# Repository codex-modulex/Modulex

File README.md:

# Modulex

All modulex listed on our webshop

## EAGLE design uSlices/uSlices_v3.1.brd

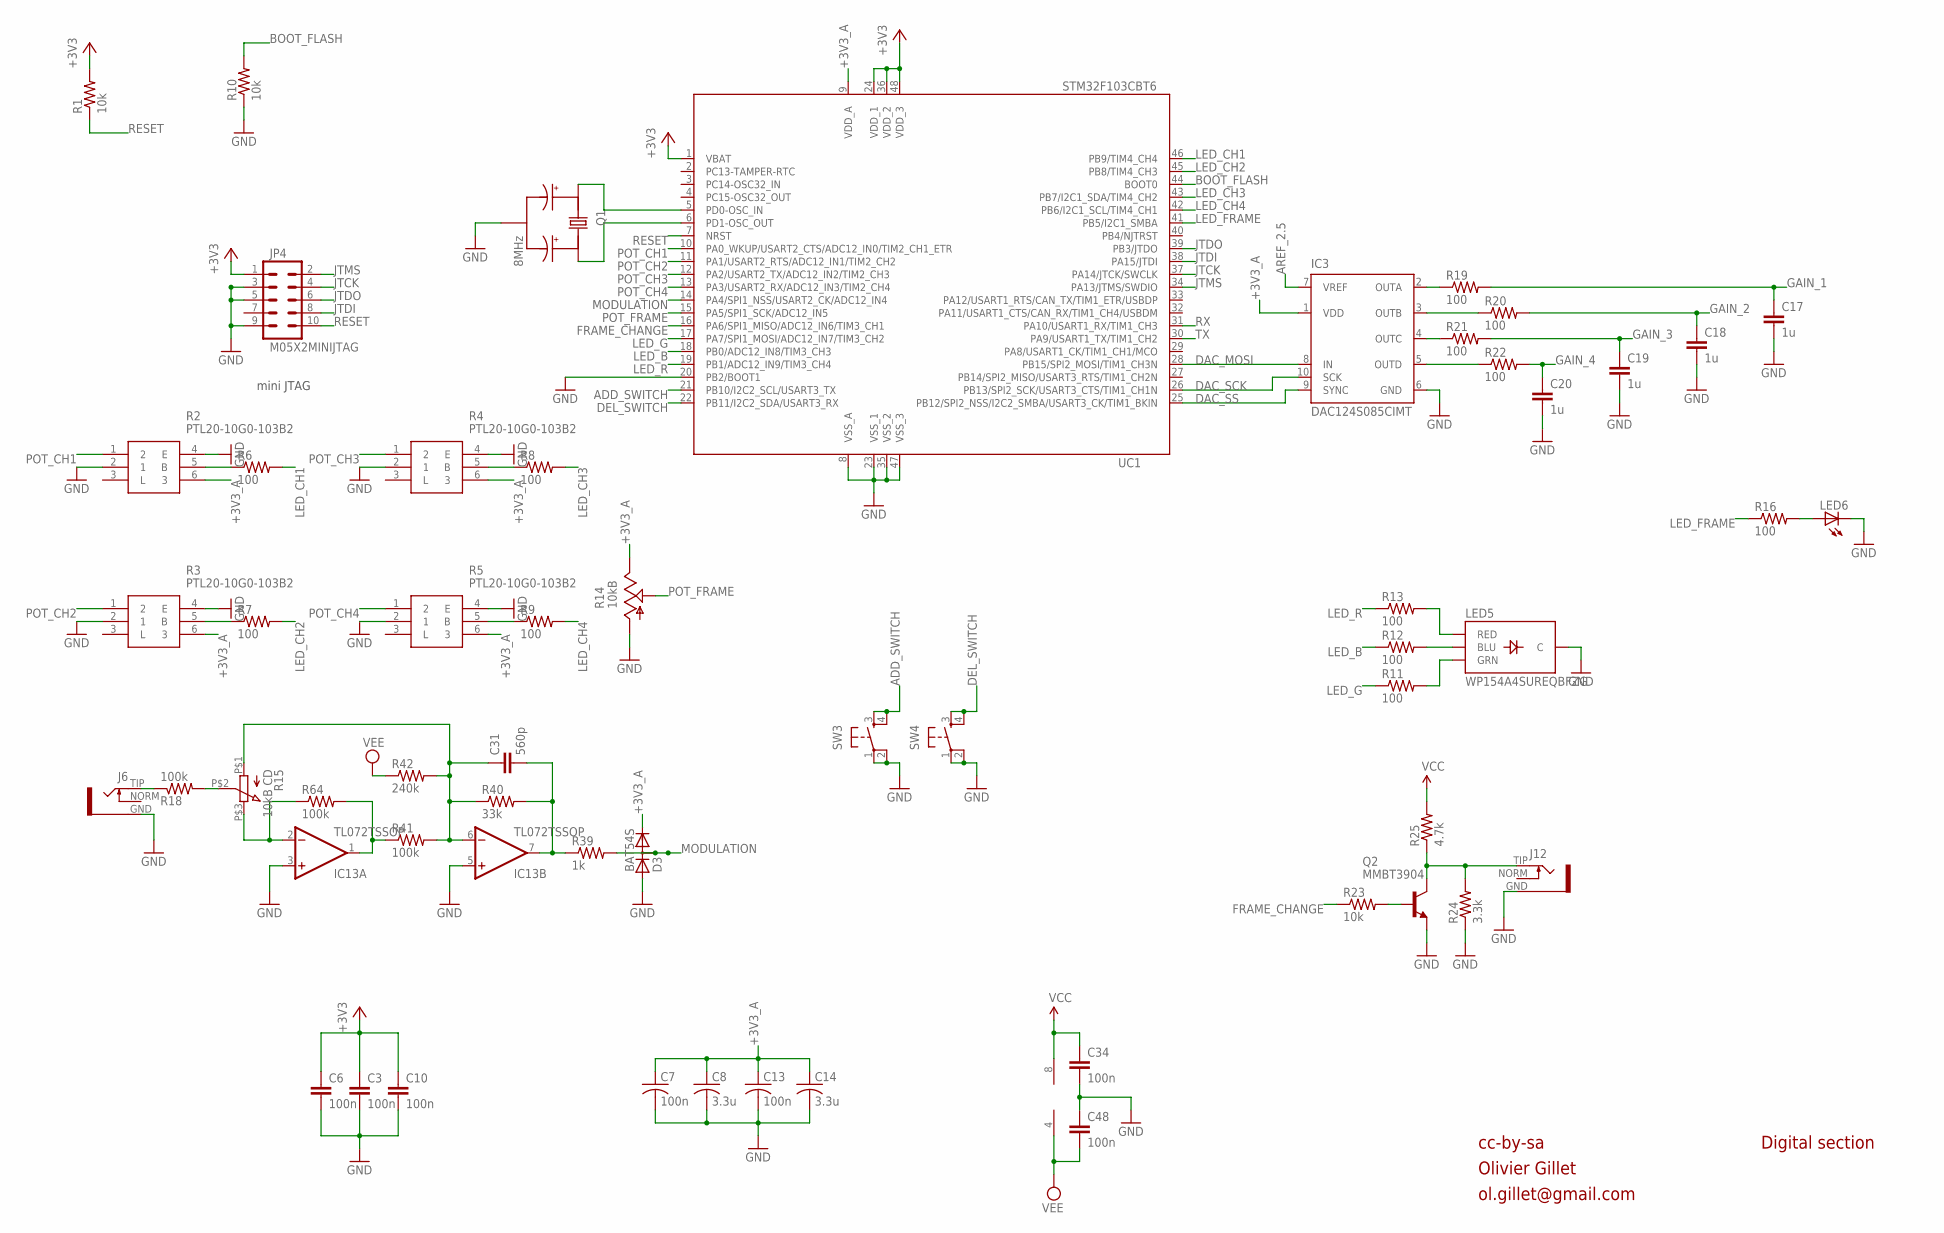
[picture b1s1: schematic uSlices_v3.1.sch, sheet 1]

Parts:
C3, C6, C10, C34, C48: 100n; PARTS_AMAN_RESISTOR_0603
C7, C13: 100n; C0603
C8, C14: 3.3u; C0603
C17, C18, C19, C20: 1u; PARTS_AMAN_RESISTOR_0603
C31: 560p; PARTS_AMAN_RESISTOR_0603
D3: BAT54S; SOT23
IC3: DAC124S085CIMT; MSOP10
IC13: TL072TSSOP; TSSOP-8
J6, J12: INSTRUO_S_JACK_S2_INV
JP4: M05X2MINIJTAG; 2X5-1.27
LED5: WP154A4SUREQBFZG; LED-TRICOLOR-THROUGHHOLE
LED6: LED3MM
Q1: 8MHz; INSTRUO_CRYSTAL_SMALLER
Q2: MMBT3904; SOT23-BEC
R1, R10, R23: 10k; PARTS_AMAN_RESISTOR_0603
R2, R3, R4, R5: PTL20-10G0-103B2; PTL2010G0103B2
R6, R7, R8, R9, R11, R12, R13, R16, R19, R20, R21, R22: 100; PARTS_AMAN_RESISTOR_0603
R14: 10kB; ALPS_POT_VERTICAL_PS
R15: 10kB CD; INSTRUO_Q-POT2
R18: 100k; R0603
R24: 3.3k; PARTS_AMAN_RESISTOR_0603
R25: 4.7k; PARTS_AMAN_RESISTOR_0603
R39: 1k; PARTS_AMAN_RESISTOR_0603
R40: 33k; PARTS_AMAN_RESISTOR_0603
R41, R64: 100k; PARTS_AMAN_RESISTOR_0603
R42: 240k; PARTS_AMAN_RESISTOR_0603
SW3, SW4: SPARKFUN_TAC_SWITCHPTH; SPARKFUN_TACTILE-PTH
UC1: STM32F103CBT6; LQFP48

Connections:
+3V3: C3.1, C6.1, C10.1, JP4.1, R1.2, UC1.1 (VBAT), UC1.24 (VDD_1), UC1.36 (VDD_2), UC1.48 (VDD_3); also elsewhere on the board
+3V3_A: C7.1, C8.1, C13.1, C14.1, D3.2 (C), IC3.1 (VDD), R2.6 (3), R3.6 (3), R4.6 (3), R5.6 (3), R14.P$1 (E), UC1.9 (VDD_A); also elsewhere on the board
ADD_SWITCH: SW3.3, SW3.4, UC1.21 (PB10/I2C2_SCL/USART3_TX)
AREF_2.5: IC3.7 (VREF); also elsewhere on the board
BOOT_FLASH: R10.2, UC1.44 (BOOT0)
DAC_MOSI: IC3.8 (IN), UC1.28 (PB15/SPI2_MOSI/TIM1_CH3N)
DAC_SCK: IC3.10 (SCK), UC1.26 (PB13/SPI2_SCK/USART3_CTS/TIM1_CH1N)
DAC_SS: IC3.9 (SYNC), UC1.25 (PB12/SPI2_NSS/I2C2_SMBA/USART3_CK/TIM1_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)
DEL_SWITCH: SW4.3, SW4.4, UC1.22 (PB11/I2C2_SDA/USART3_RX)
FRAME_CHANGE: R23.1, UC1.16 (PA6/SPI1_MISO/ADC12_IN6/TIM3_CH1)
GAIN_1: C17.1, R19.2; also elsewhere on the board
GAIN_2: C18.1, R20.2; also elsewhere on the board
GAIN_3: C19.1, R21.2; also elsewhere on the board
GAIN_4: C20.1, R22.2; also elsewhere on the board
GND: C3.2, C6.2, C7.2, C8.2, C10.2, C13.2, C14.2, C17.2, C18.2, C19.2, C20.2, C34.2, C48.1, D3.1 (A), IC3.6 (GND), IC13.3 (+IN), IC13.5 (+IN), J6.GND, J12.GND, JP4.3, JP4.5, JP4.9, LED5.GND (C), LED6.K (C), Q1.GND, Q2.E, R2.2 (1), R2.4 (E), R3.2 (1), R3.4 (E), R4.2 (1), R4.4 (E), R5.2 (1), R5.4 (E), R10.1, R14.P$3 (A), R24.1, SW3.1, SW3.2, SW4.1, SW4.2, UC1.8 (VSS_A), UC1.20 (PB2/BOOT1), UC1.23 (VSS_1), UC1.35 (VSS_2), UC1.47 (VSS_3); also elsewhere on the board
JTCK: JP4.4, UC1.37 (PA14/JTCK/SWCLK)
JTDI: JP4.8, UC1.38 (PA15/JTDI)
JTDO: JP4.6, UC1.39 (PB3/JTDO)
JTMS: JP4.2, UC1.34 (PA13/JTMS/SWDIO)
LED_B: R12.1, UC1.18 (PB0/ADC12_IN8/TIM3_CH3)
LED_CH1: R6.2, UC1.46 (PB9/TIM4_CH4)
LED_CH2: R7.2, UC1.45 (PB8/TIM4_CH3)
LED_CH3: R8.2, UC1.43 (PB7/I2C1_SDA/TIM4_CH2)
LED_CH4: R9.2, UC1.42 (PB6/I2C1_SCL/TIM4_CH1)
LED_FRAME: R16.1, UC1.41 (PB5/I2C1_SMBA)
LED_G: R11.1, UC1.17 (PA7/SPI1_MOSI/ADC12_IN7/TIM3_CH2)
LED_R: R13.1, UC1.19 (PB1/ADC12_IN9/TIM3_CH4)
MODULATION: D3.3 (AC), R39.2, UC1.14 (PA4/SPI1_NSS/USART2_CK/ADC12_IN4)
unnamed: IC13.2 (-IN), R15.P$3 (3), R64.1
unnamed: R15.P$2 (2), R18.2
unnamed: R2.5 (B), R6.1
unnamed: Q1.X1, UC1.5 (PD0-OSC_IN)
unnamed: Q1.X2, UC1.6 (PD1-OSC_OUT)
unnamed: IC13.1 (OUT), R41.1, R64.2
unnamed: J6.TIP, R18.1
unnamed: C31.2, IC13.7 (OUT), R39.1, R40.2
unnamed: C31.1, IC13.6 (-IN), R15.P$1 (1), R40.1, R41.2, R42.2
unnamed: LED6.A, R16.2
unnamed: LED5.RED, R13.2
unnamed: LED5.BLU, R12.2
unnamed: LED5.GRN, R11.2
unnamed: R3.5 (B), R7.1
unnamed: IC3.2 (OUTA), R19.1
unnamed: IC3.3 (OUTB), R20.1
unnamed: IC3.4 (OUTC), R21.1
unnamed: J12.TIP, Q2.C, R24.2, R25.1
unnamed: IC3.5 (OUTD), R22.1
unnamed: R4.5 (B), R8.1
unnamed: Q2.B, R23.2
unnamed: R5.5 (B), R9.1
POT_CH1: R2.1 (2), UC1.10 (PA0_WKUP/USART2_CTS/ADC12_IN0/TIM2_CH1_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)
POT_CH2: R3.1 (2), UC1.11 (PA1/USART2_RTS/ADC12_IN1/TIM2_CH2)
POT_CH3: R4.1 (2), UC1.12 (PA2/USART2_TX/ADC12_IN2/TIM2_CH3)
POT_CH4: R5.1 (2), UC1.13 (PA3/USART2_RX/ADC12_IN3/TIM2_CH4)
POT_FRAME: R14.P$2 (S), UC1.15 (PA5/SPI1_SCK/ADC12_IN5)
RESET: JP4.10, R1.1, UC1.7 (NRST)
RX: UC1.31 (PA10/USART1_RX/TIM1_CH3)
TX: UC1.30 (PA9/USART1_TX/TIM1_CH2)
VCC: C34.1, IC13.8 (V+), R25.2; also elsewhere on the board
VEE: C48.2, IC13.4 (V-), R42.1; also elsewhere on the board

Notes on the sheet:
cc-by-sa
Olivier Gillet
ol.gillet@gmail.com
mini JTAG
Digital section

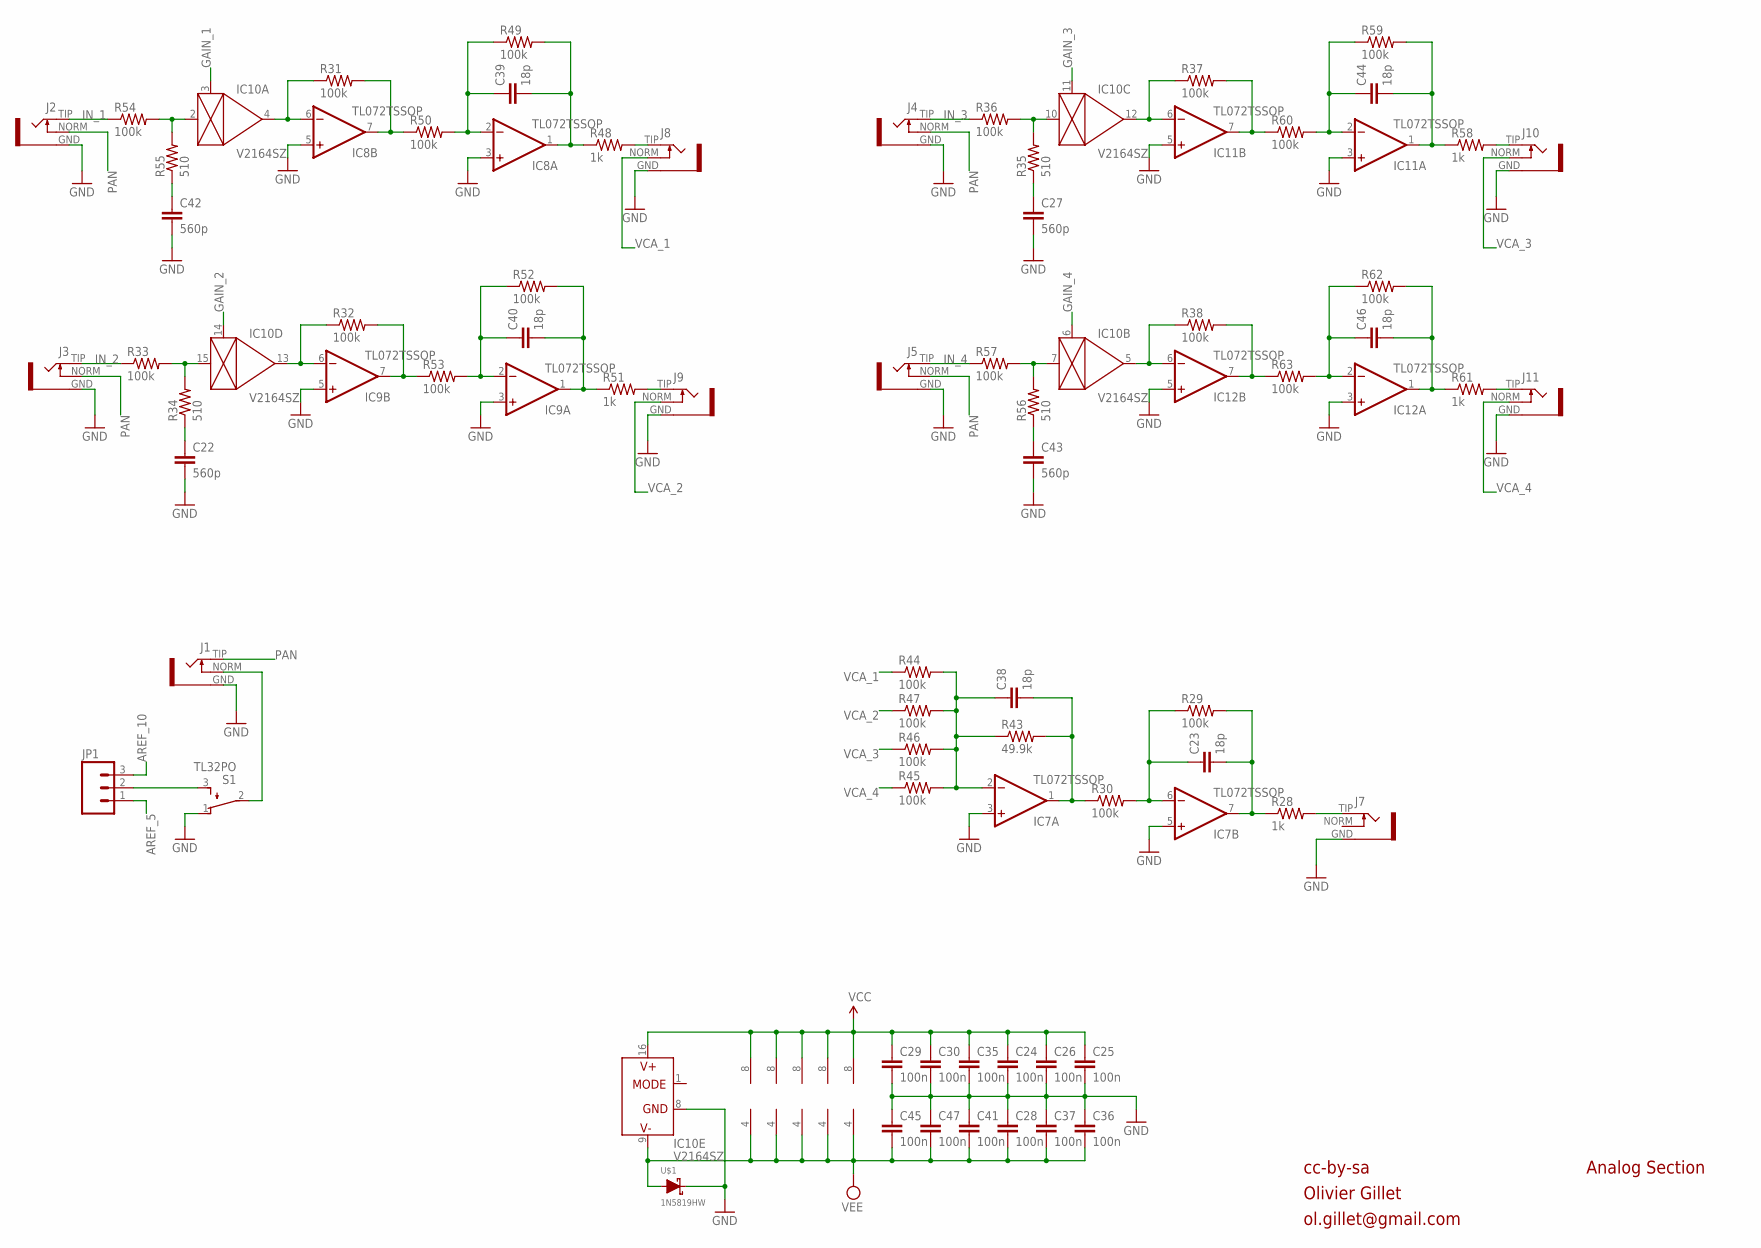
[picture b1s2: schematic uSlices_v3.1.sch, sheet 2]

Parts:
C22, C27, C42, C43: 560p; PARTS_AMAN_RESISTOR_0603
C23, C38, C39, C40, C44, C46: 18p; PARTS_AMAN_RESISTOR_0603
C24, C25, C26, C28, C29, C30, C35, C36, C37, C41, C45, C47: 100n; PARTS_AMAN_RESISTOR_0603
IC7, IC8, IC9, IC11, IC12: TL072TSSOP; TSSOP-8
IC10: V2164SZ; SOIC16N
J1, J2, J3, J4, J5, J7, J8, J9, J10, J11: INSTRUO_S_JACK_S2_INV
JP1: M03PTH; 1X03
R28, R48, R51, R58, R61: 1k; PARTS_AMAN_RESISTOR_0603
R29, R30, R31, R32, R33, R36, R37, R38, R44, R45, R46, R47, R49, R50, R52, R53, R54, R57, R59, R60, R62, R63: 100k; PARTS_AMAN_RESISTOR_0603
R34, R35, R55, R56: 510; PARTS_AMAN_RESISTOR_0603
R43: 49.9k; PARTS_AMAN_RESISTOR_0603
S1: TL32PO; TL3XPO
U$1: 1N5819HW; SOD123

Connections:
AREF_5: JP1.1; also elsewhere on the board
AREF_10: JP1.3; also elsewhere on the board
FB_CURRENT: IC10.2 (IN), R54.2, R55.2
FB_CURRENT1: IC10.15 (IN), R33.2, R34.2
FB_CURRENT2: IC10.10 (IN), R35.2, R36.2
FB_CURRENT3: IC10.7 (IN), R56.2, R57.2
GAIN_1: IC10.3 (CTRL); also elsewhere on the board
GAIN_2: IC10.14 (CTRL); also elsewhere on the board
GAIN_3: IC10.11 (CTRL); also elsewhere on the board
GAIN_4: IC10.6 (CTRL); also elsewhere on the board
GND: C22.2, C24.2, C25.2, C26.2, C27.2, C28.1, C29.2, C30.2, C35.2, C36.1, C37.1, C41.1, C42.2, C43.2, C45.1, C47.1, IC7.3 (+IN), IC7.5 (+IN), IC8.3 (+IN), IC8.5 (+IN), IC9.3 (+IN), IC9.5 (+IN), IC10.8 (GND), IC11.3 (+IN), IC11.5 (+IN), IC12.3 (+IN), IC12.5 (+IN), J1.GND, J2.GND, J3.GND, J4.GND, J5.GND, J7.GND, J8.GND, J9.GND, J10.GND, J11.GND, S1.1 (O), U$1.C (K); also elsewhere on the board
IN_1: J2.TIP, R54.1
IN_2: J3.TIP, R33.1
IN_3: J4.TIP, R36.1
IN_4: J5.TIP, R57.1
unnamed: C42.1, R55.1
unnamed: J7.TIP, R28.2
unnamed: IC9.7 (OUT), R32.2, R53.1
unnamed: C27.1, R35.1
unnamed: IC8.6 (-IN), IC10.4 (OUT), R31.1
unnamed: C39.1, IC8.2 (-IN), R49.1, R50.2
unnamed: C39.2, IC8.1 (OUT), R48.1, R49.2
unnamed: C23.2, IC7.7 (OUT), R28.1, R29.2
unnamed: C22.1, R34.1
unnamed: C38.1, IC7.2 (-IN), R43.1, R44.2, R45.2, R46.2, R47.2
unnamed: IC9.6 (-IN), IC10.13 (OUT), R32.1
unnamed: C23.1, IC7.6 (-IN), R29.1, R30.2
unnamed: C40.1, IC9.2 (-IN), R52.1, R53.2
unnamed: C40.2, IC9.1 (OUT), R51.1, R52.2
unnamed: IC10.12 (OUT), IC11.6 (-IN), R37.1
unnamed: C44.1, IC11.2 (-IN), R59.1, R60.2
unnamed: C44.2, IC11.1 (OUT), R58.1, R59.2
unnamed: C43.1, R56.1
unnamed: C38.2, IC7.1 (OUT), R30.1, R43.2
unnamed: IC10.5 (OUT), IC12.6 (-IN), R38.1
unnamed: C46.1, IC12.2 (-IN), R62.1, R63.2
unnamed: C46.2, IC12.1 (OUT), R61.1, R62.2
unnamed: J1.NORM, S1.2
unnamed: J8.TIP, R48.2
unnamed: JP1.2, S1.3 (S)
unnamed: IC12.7 (OUT), R38.2, R63.1
unnamed: J9.TIP, R51.2
unnamed: J11.TIP, R61.2
unnamed: J10.TIP, R58.2
PAN: J1.TIP, J2.NORM, J3.NORM, J4.NORM, J5.NORM
VCA0_1: IC8.7 (OUT), R31.2, R50.1
VCA0_3: IC11.7 (OUT), R37.2, R60.1
VCA_1: J8.NORM, R44.1
VCA_2: J9.NORM, R47.1
VCA_3: J10.NORM, R46.1
VCA_4: J11.NORM, R45.1
VCC: C24.1, C25.1, C26.1, C29.1, C30.1, C35.1, IC7.8 (V+), IC8.8 (V+), IC9.8 (V+), IC10.16 (V+), IC11.8 (V+), IC12.8 (V+); also elsewhere on the board
VEE: C28.2, C36.2, C37.2, C41.2, C45.2, C47.2, IC7.4 (V-), IC8.4 (V-), IC9.4 (V-), IC10.9 (V-), IC11.4 (V-), IC12.4 (V-), U$1.A; also elsewhere on the board

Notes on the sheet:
cc-by-sa
Olivier Gillet
ol.gillet@gmail.com
Analog Section

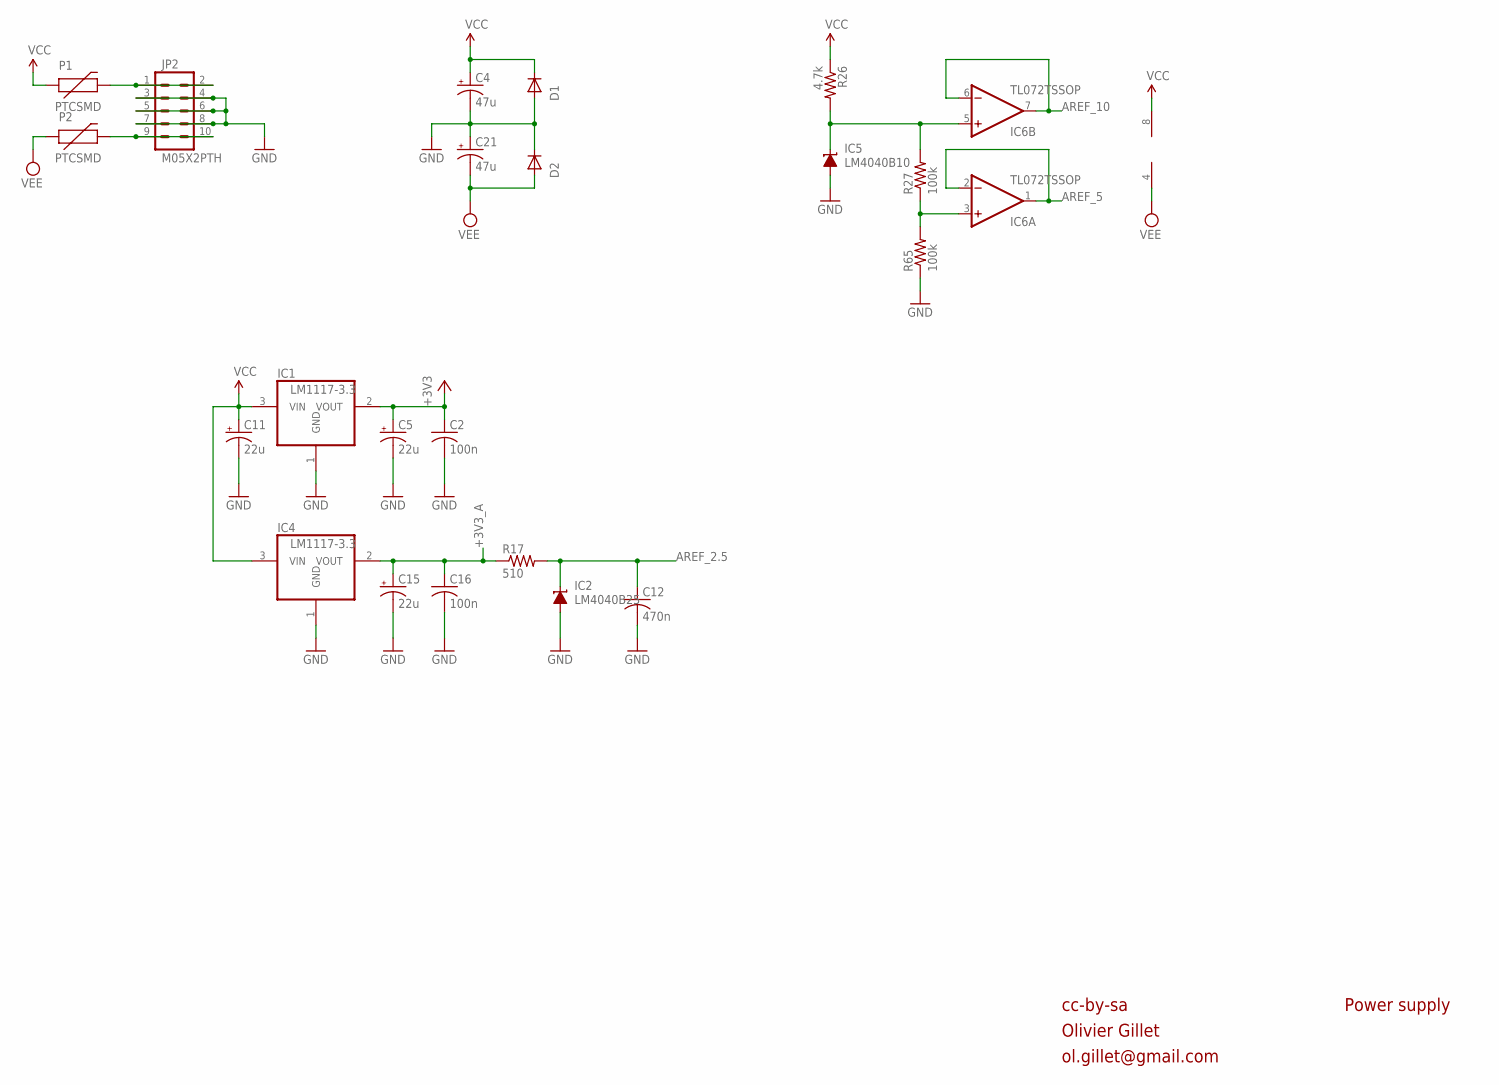
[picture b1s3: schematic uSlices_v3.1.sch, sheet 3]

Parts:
C2, C16: 100n; C0603
C4, C21: 47u; PANASONIC_D
C5, C11, C15: 22u; PANASONIC_C
C12: 470n; C0603
D1, D2: 1N5819HW; SOD123
IC1, IC4: LM1117-3.3; SOT223
IC2: LM4040B25; DBZ_R-PDSO-G3
IC5: LM4040B10; DBZ_R-PDSO-G3
IC6: TL072TSSOP; TSSOP-8
JP2: M05X2PTH; AVR_ICSP
P1, P2: PTCSMD; PTC-1206
R17: 510; R0603
R26: 4.7k; R0603
R27, R65: 100k; R0603

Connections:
+3V3: C2.1, C5.+, IC1.2 (VOUT); also elsewhere on the board
+3V3_A: C15.+, C16.1, IC4.2 (VOUT), R17.1; also elsewhere on the board
AREF_2.5: C12.1, IC2.1 (C), R17.2; also elsewhere on the board
AREF_5: IC6.1 (OUT), IC6.2 (-IN); also elsewhere on the board
AREF_10: IC6.6 (-IN), IC6.7 (OUT); also elsewhere on the board
AREF_10_0: IC5.1 (C), IC6.5 (+IN), R26.2, R27.2
GND: C2.2, C4.-, C5.-, C11.-, C12.2, C15.-, C16.2, C21.+, D1.A, D2.C, IC1.1 (GND), IC2.2 (A), IC4.1 (GND), IC5.2 (A), JP2.3, JP2.4, JP2.5, JP2.6, JP2.7, JP2.8, R65.1; also elsewhere on the board
unnamed: IC6.3 (+IN), R27.1, R65.2
unnamed: JP2.1, JP2.2, P1.2
unnamed: JP2.9, JP2.10, P2.2
VCC: C4.+, C11.+, D1.C, IC1.3 (VIN), IC4.3 (VIN), IC6.8 (V+), P1.1, R26.1; also elsewhere on the board
VEE: C21.-, D2.A, IC6.4 (V-), P2.1; also elsewhere on the board

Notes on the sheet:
cc-by-sa
Olivier Gillet
ol.gillet@gmail.com
Power supply

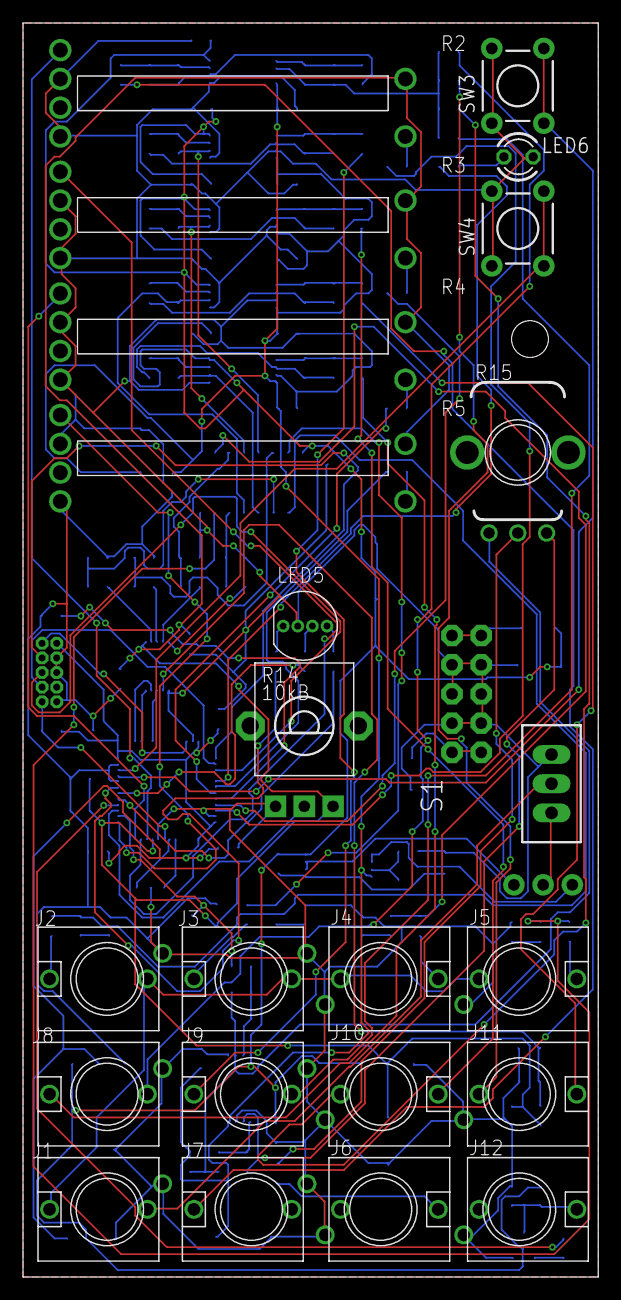
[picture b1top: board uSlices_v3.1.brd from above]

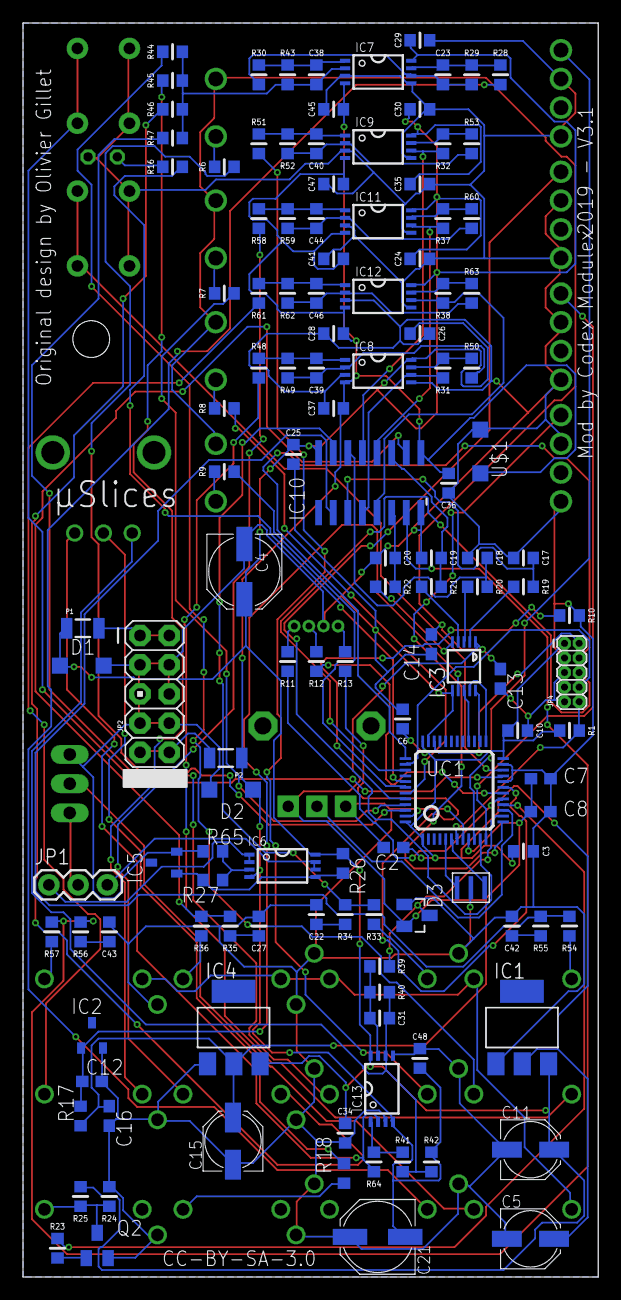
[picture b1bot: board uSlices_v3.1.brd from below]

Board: 2 copper layers, 50.0 x 109.0 mm, 151 parts (128 on the bottom side), 108 nets.

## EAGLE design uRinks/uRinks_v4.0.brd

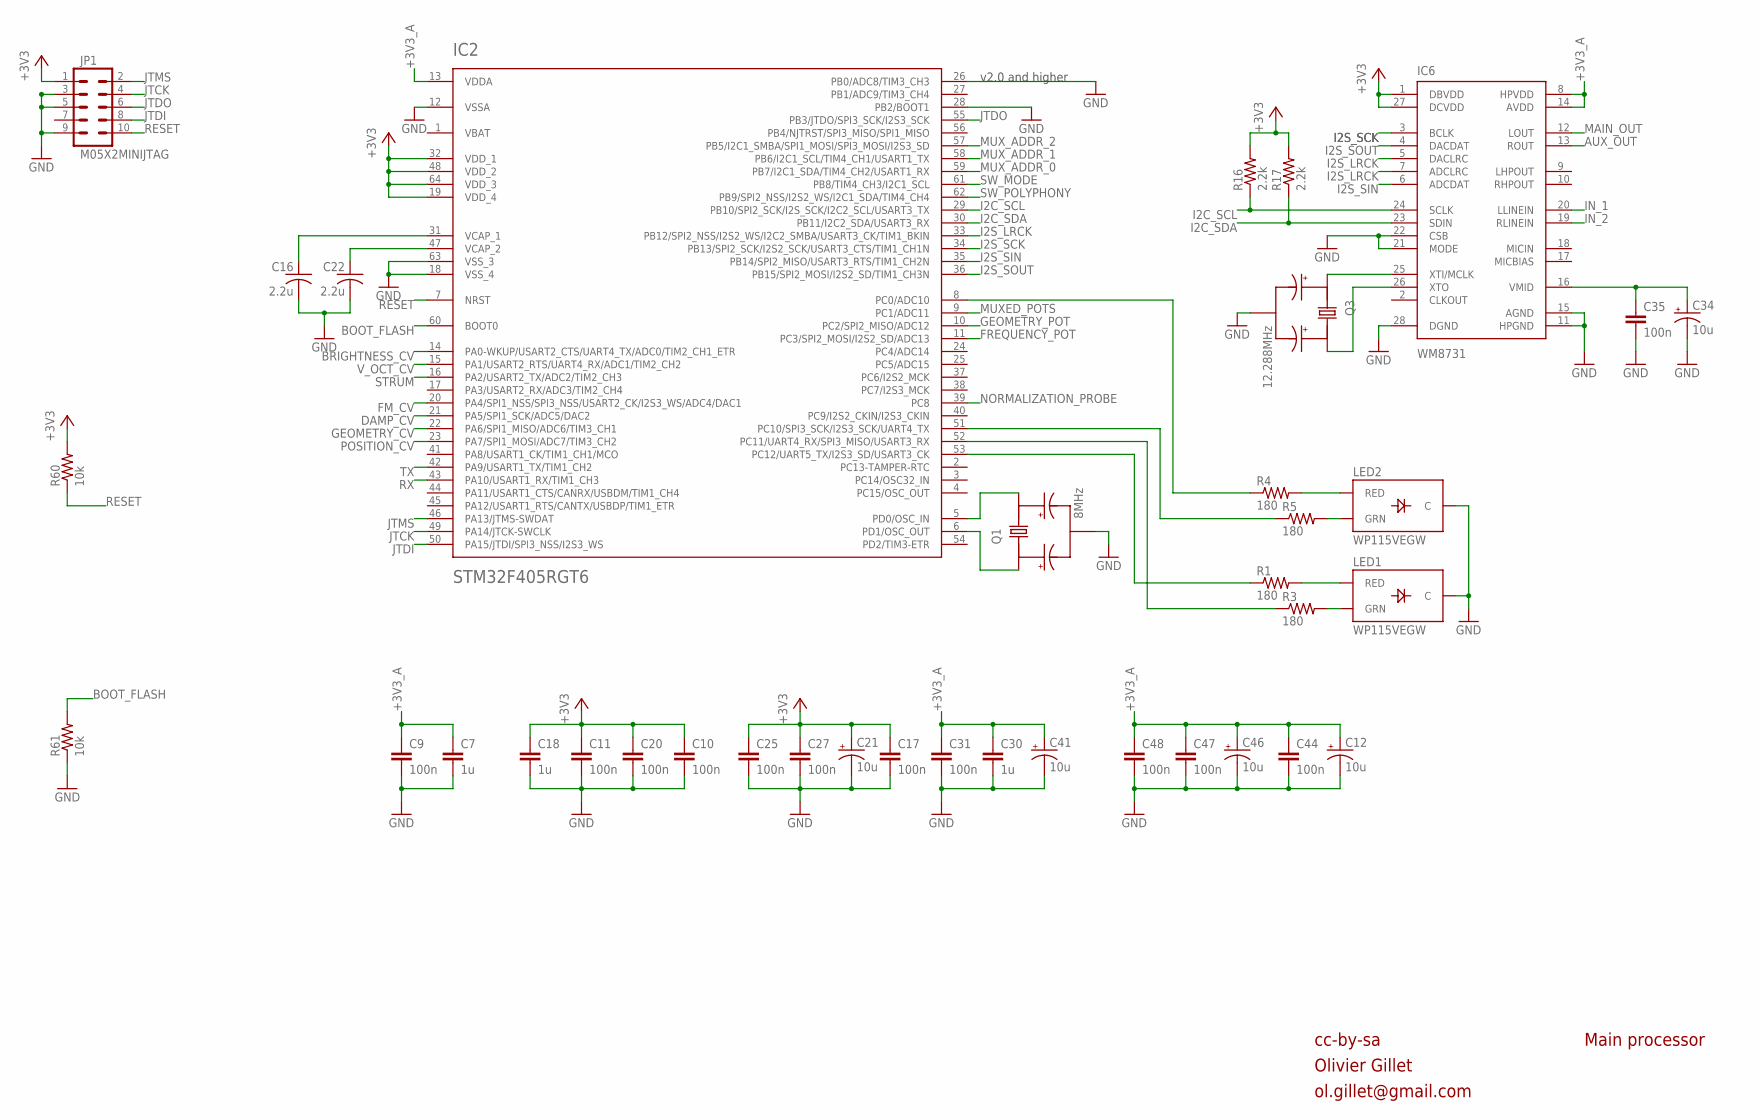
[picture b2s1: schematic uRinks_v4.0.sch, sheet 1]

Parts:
C7, C18, C30: 1u; PARTS_AMAN_RESISTOR_0603
C9, C10, C11, C17, C20, C25, C27, C31, C35, C44, C47, C48: 100n; PARTS_AMAN_RESISTOR_0603
C12, C21, C34, C41, C46: 10u; PANASONIC_A
C16, C22: 2.2u; C0805
IC2: STM32F405RGT6; TQFP-10X10-64
IC6: WM8731; SSOP28
JP1: M05X2MINIJTAG; 2X5-1.27
LED1, LED2: WP115VEGW; LED-BICOLOR-THROUGHHOLE
Q1: 8MHz; INSTRUO_CRYSTAL_SMALLER
Q3: 12.288MHz; INSTRUO_CRYSTAL_SMALLER
R1, R3, R4, R5: 180; PARTS_AMAN_RESISTOR_0603
R16, R17: 2.2k; PARTS_AMAN_RESISTOR_0603
R60, R61: 10k; PARTS_AMAN_RESISTOR_0603

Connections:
+3V3: C10.1, C11.1, C17.1, C18.1, C20.1, C21.+, C25.1, C27.1, IC2.19 (VDD_4), IC2.32 (VDD_1), IC2.48 (VDD_2), IC2.64 (VDD_3), IC6.1 (DBVDD), IC6.27 (DCVDD), JP1.1, R16.2, R17.2, R60.2; also elsewhere on the board
+3V3_A: C7.1, C9.1, C12.+, C30.1, C31.1, C41.+, C44.1, C46.+, C47.1, C48.1, IC2.13 (VDDA), IC6.8 (HPVDD), IC6.14 (AVDD); also elsewhere on the board
AUX_OUT: IC6.13 (ROUT); also elsewhere on the board
BOOT_FLASH: IC2.60 (BOOT0), R61.2
BRIGHTNESS_CV: IC2.14 (PA0-WKUP/USART2_CTS/UART4_TX/ADC0/TIM2_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); also elsewhere on the board
DAMP_CV: IC2.21 (PA5/SPI1_SCK/ADC5/DAC2); also elsewhere on the board
FM_CV: IC2.20 (PA4/SPI1_NSS/SPI3_NSS/USART2_CK/I2S3_WS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); also elsewhere on the board
FREQUENCY_POT: IC2.11 (PC3/SPI2_MOSI/I2S2_SD/ADC13); also elsewhere on the board
GEOMETRY_CV: IC2.22 (PA6/SPI1_MISO/ADC6/TIM3_CH1); also elsewhere on the board
GEOMETRY_POT: IC2.10 (PC2/SPI2_MISO/ADC12); also elsewhere on the board
GND: C7.2, C9.2, C10.2, C11.2, C12.-, C16.2, C17.2, C18.2, C20.2, C21.-, C22.2, C25.2, C27.2, C30.2, C31.2, C34.-, C35.2, C41.-, C44.2, C46.-, C47.2, C48.2, IC2.12 (VSSA), IC2.18 (VSS_4), IC2.26 (PB0/ADC8/TIM3_CH3), IC2.28 (PB2/BOOT1), IC2.63 (VSS_3), IC6.11 (HPGND), IC6.15 (AGND), IC6.21 (MODE), IC6.22 (CSB), IC6.28 (DGND), JP1.3, JP1.5, JP1.9, LED1.2 (C), LED2.2 (C), Q1.GND, Q3.GND, R61.1; also elsewhere on the board
I2C_SCL: IC2.29 (PB10/SPI2_SCK/I2S_SCK/I2C2_SCL/USART3_TX), IC6.24 (SCLK), R16.1
I2C_SDA: IC2.30 (PB11/I2C2_SDA/USART3_RX), IC6.23 (SDIN), R17.1
I2S_LRCK: IC2.33 (PB12/SPI2_NSS/I2S2_WS/I2C2_SMBA/USART3_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), IC6.5 (DACLRC), IC6.7 (ADCLRC)
I2S_SCK: IC2.34 (PB13/SPI2_SCK/I2S2_SCK/USART3_CTS/TIM1_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), IC6.3 (BCLK)
I2S_SIN: IC2.35 (PB14/SPI2_MISO/USART3_RTS/TIM1_CH2N), IC6.6 (ADCDAT)
I2S_SOUT: IC2.36 (PB15/SPI2_MOSI/I2S2_SD/TIM1_CH3N), IC6.4 (DACDAT)
IN_1: IC6.20 (LLINEIN); also elsewhere on the board
IN_2: IC6.19 (RLINEIN); also elsewhere on the board
JTCK: IC2.49 (PA14/JTCK-SWCLK), JP1.4
JTDI: IC2.50 (PA15/JTDI/SPI3_NSS/I2S3_WS), JP1.8
JTDO: IC2.55 (PB3/JTDO/SPI3_SCK/I2S3_SCK), JP1.6
JTMS: IC2.46 (PA13/JTMS-SWDAT), JP1.2
MAIN_OUT: IC6.12 (LOUT); also elsewhere on the board
MUXED_POTS: IC2.9 (PC1/ADC11); also elsewhere on the board
MUX_ADDR_0: IC2.59 (PB7/I2C1_SDA/TIM4_CH2/USART1_RX); also elsewhere on the board
MUX_ADDR_1: IC2.58 (PB6/I2C1_SCL/TIM4_CH1/USART1_TX); also elsewhere on the board
MUX_ADDR_2: IC2.57 (PB5/I2C1_SMBA/SPI1_MOSI/SPI3_MOSI/I2S3_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); also elsewhere on the board
unnamed: IC2.6 (PD1/OSC_OUT), Q1.X1
unnamed: IC2.5 (PD0/OSC_IN), Q1.X2
unnamed: LED1.3 (RED), R1.2
unnamed: C22.1, IC2.47 (VCAP_2)
unnamed: C34.+, C35.1, IC6.16 (VMID)
unnamed: C16.1, IC2.31 (VCAP_1)
unnamed: LED1.1 (GRN), R3.2
unnamed: LED2.3 (RED), R4.2
unnamed: LED2.1 (GRN), R5.2
unnamed: IC2.52 (PC11/UART4_RX/SPI3_MISO/USART3_RX), R3.1
unnamed: IC2.8 (PC0/ADC10), R4.1
unnamed: IC6.25 (XTI/MCLK), Q3.X1
unnamed: IC6.26 (XTO), Q3.X2
unnamed: IC2.53 (PC12/UART5_TX/I2S3_SD/USART3_CK), R1.1
unnamed: IC2.51 (PC10/SPI3_SCK/I2S3_SCK/UART4_TX), R5.1
NORMALIZATION_PROBE: IC2.39 (PC8); also elsewhere on the board
POSITION_CV: IC2.23 (PA7/SPI1_MOSI/ADC7/TIM3_CH2); also elsewhere on the board
RESET: IC2.7 (NRST), JP1.10, R60.1
RX: IC2.43 (PA10/USART1_RX/TIM1_CH3)
STRUM: IC2.16 (PA2/USART2_TX/ADC2/TIM2_CH3); also elsewhere on the board
SW_MODE: IC2.61 (PB8/TIM4_CH3/I2C1_SCL); also elsewhere on the board
SW_POLYPHONY: IC2.62 (PB9/SPI2_NSS/I2S2_WS/I2C1_SDA/TIM4_CH4); also elsewhere on the board
TX: IC2.42 (PA9/USART1_TX/TIM1_CH2)
VBAT: IC2.1 (VBAT)
V_OCT_CV: IC2.15 (PA1/USART2_RTS/UART4_RX/ADC1/TIM2_CH2); also elsewhere on the board

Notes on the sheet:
cc-by-sa
Olivier Gillet
ol.gillet@gmail.com
Main processor
v2.0 and higher

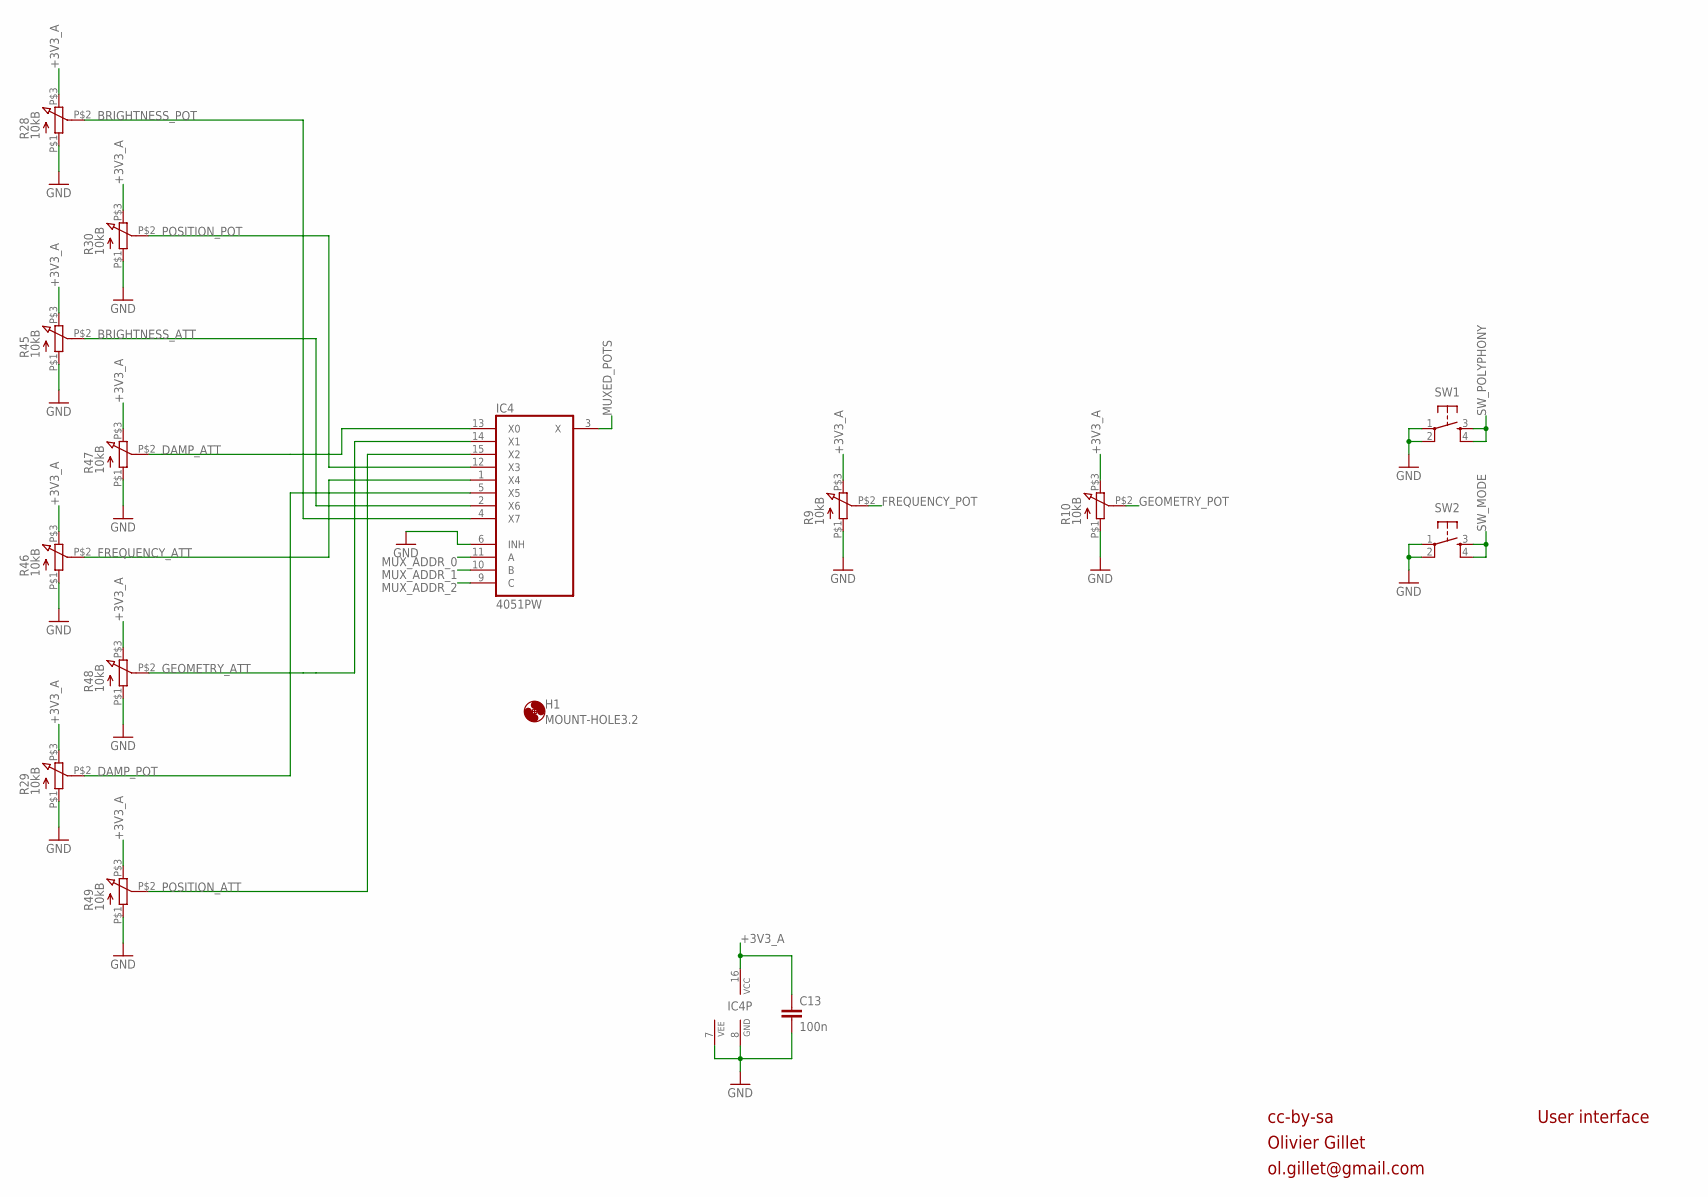
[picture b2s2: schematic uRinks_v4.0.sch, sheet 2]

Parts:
C13: 100n; PARTS_AMAN_RESISTOR_0603
H1: MOUNT-HOLE3.2; 3,2
IC4: 4051PW; TSSOP16
R9, R10, R28, R29, R30, R45, R46, R47, R48, R49: 10kB; INSTRUO_Q-POT2
SW1, SW2: TAC_SWITCHPTH; TACTILE-PTH

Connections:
+3V3_A: C13.1, IC4.16 (VCC), R9.P$3 (3), R10.P$3 (3), R28.P$3 (3), R29.P$3 (3), R30.P$3 (3), R45.P$3 (3), R46.P$3 (3), R47.P$3 (3), R48.P$3 (3), R49.P$3 (3); also elsewhere on the board
BRIGHTNESS_ATT: IC4.2 (X6), R45.P$2 (2)
BRIGHTNESS_POT: IC4.4 (X7), R28.P$2 (2)
DAMP_ATT: IC4.13 (X0), R47.P$2 (2)
DAMP_POT: IC4.5 (X5), R29.P$2 (2)
FREQUENCY_ATT: IC4.1 (X4), R46.P$2 (2)
FREQUENCY_POT: R9.P$2 (2); also elsewhere on the board
GEOMETRY_ATT: IC4.14 (X1), R48.P$2 (2)
GEOMETRY_POT: R10.P$2 (2); also elsewhere on the board
GND: C13.2, IC4.6 (INH), IC4.7 (VEE), IC4.8 (GND), R9.P$1 (1), R10.P$1 (1), R28.P$1 (1), R29.P$1 (1), R30.P$1 (1), R45.P$1 (1), R46.P$1 (1), R47.P$1 (1), R48.P$1 (1), R49.P$1 (1), SW1.1, SW1.2, SW2.1, SW2.2; also elsewhere on the board
MUXED_POTS: IC4.3 (X); also elsewhere on the board
MUX_ADDR_0: IC4.11 (A); also elsewhere on the board
MUX_ADDR_1: IC4.10 (B); also elsewhere on the board
MUX_ADDR_2: IC4.9 (C); also elsewhere on the board
POSITION_ATT: IC4.15 (X2), R49.P$2 (2)
POSITION_POT: IC4.12 (X3), R30.P$2 (2)
SW_MODE: SW2.3, SW2.4; also elsewhere on the board
SW_POLYPHONY: SW1.3, SW1.4; also elsewhere on the board

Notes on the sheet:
cc-by-sa
Olivier Gillet
ol.gillet@gmail.com
User interface

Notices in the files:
uDJV/uDJV_board_2_v1.1.brd:
CC-BY-SA-3.0
